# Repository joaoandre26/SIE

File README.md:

# SIE
Trabalho desenvolvido no âmbito da UC de Sistemas de Instrumentação em Eletrónica, 4º ano MIEET, ano lectivo 2018/19
Para esclarecer alguma dúvida relativamente ao trabalho desenvolvido na UC poderá contactar um dos membros do grupo por e-mail.

/*Examples*/
Na pasta MicrocontrollerExemple-master encontra-se codigo para o qual me baseei para escrever as funções do LCD. Muito Obrigado ao desenvolvedor, foi uma grande ajuda.
Link: https://github.com/andrade824/Microcontroller-Example-Code

/*Info/Reports*/
Na pasta reports encontra-se os relatorios de todas as fases deste projecto, bem como o manual de utilizador. Deverá encontrar no manual do utilizador todas as intruções para colocar o nosso projecto em total funcionamento.

/*Elevator_PCB*/
Na pasta elevatorpcb encontra-se os gerber files para imprimir o nosso pcb, e os esquemas de montagem por nós utilizados.

/*Code*/
Na pasta Elevator_Code encontra o codigo referente ao projecto 0, assim como a versão final funcional de codigo para colocar no elevador. Existem alguns erros no codigo que poderão virificar em detalhe no report da fase 3.

Notas:
O trabalho desenvolvido que se encontra neste repositório está completamente funcional, não contemplando todas as especificações exigidas inicialmente, é o suficiente para colocar o elevador a subir e descer para qualquer um dos andares.

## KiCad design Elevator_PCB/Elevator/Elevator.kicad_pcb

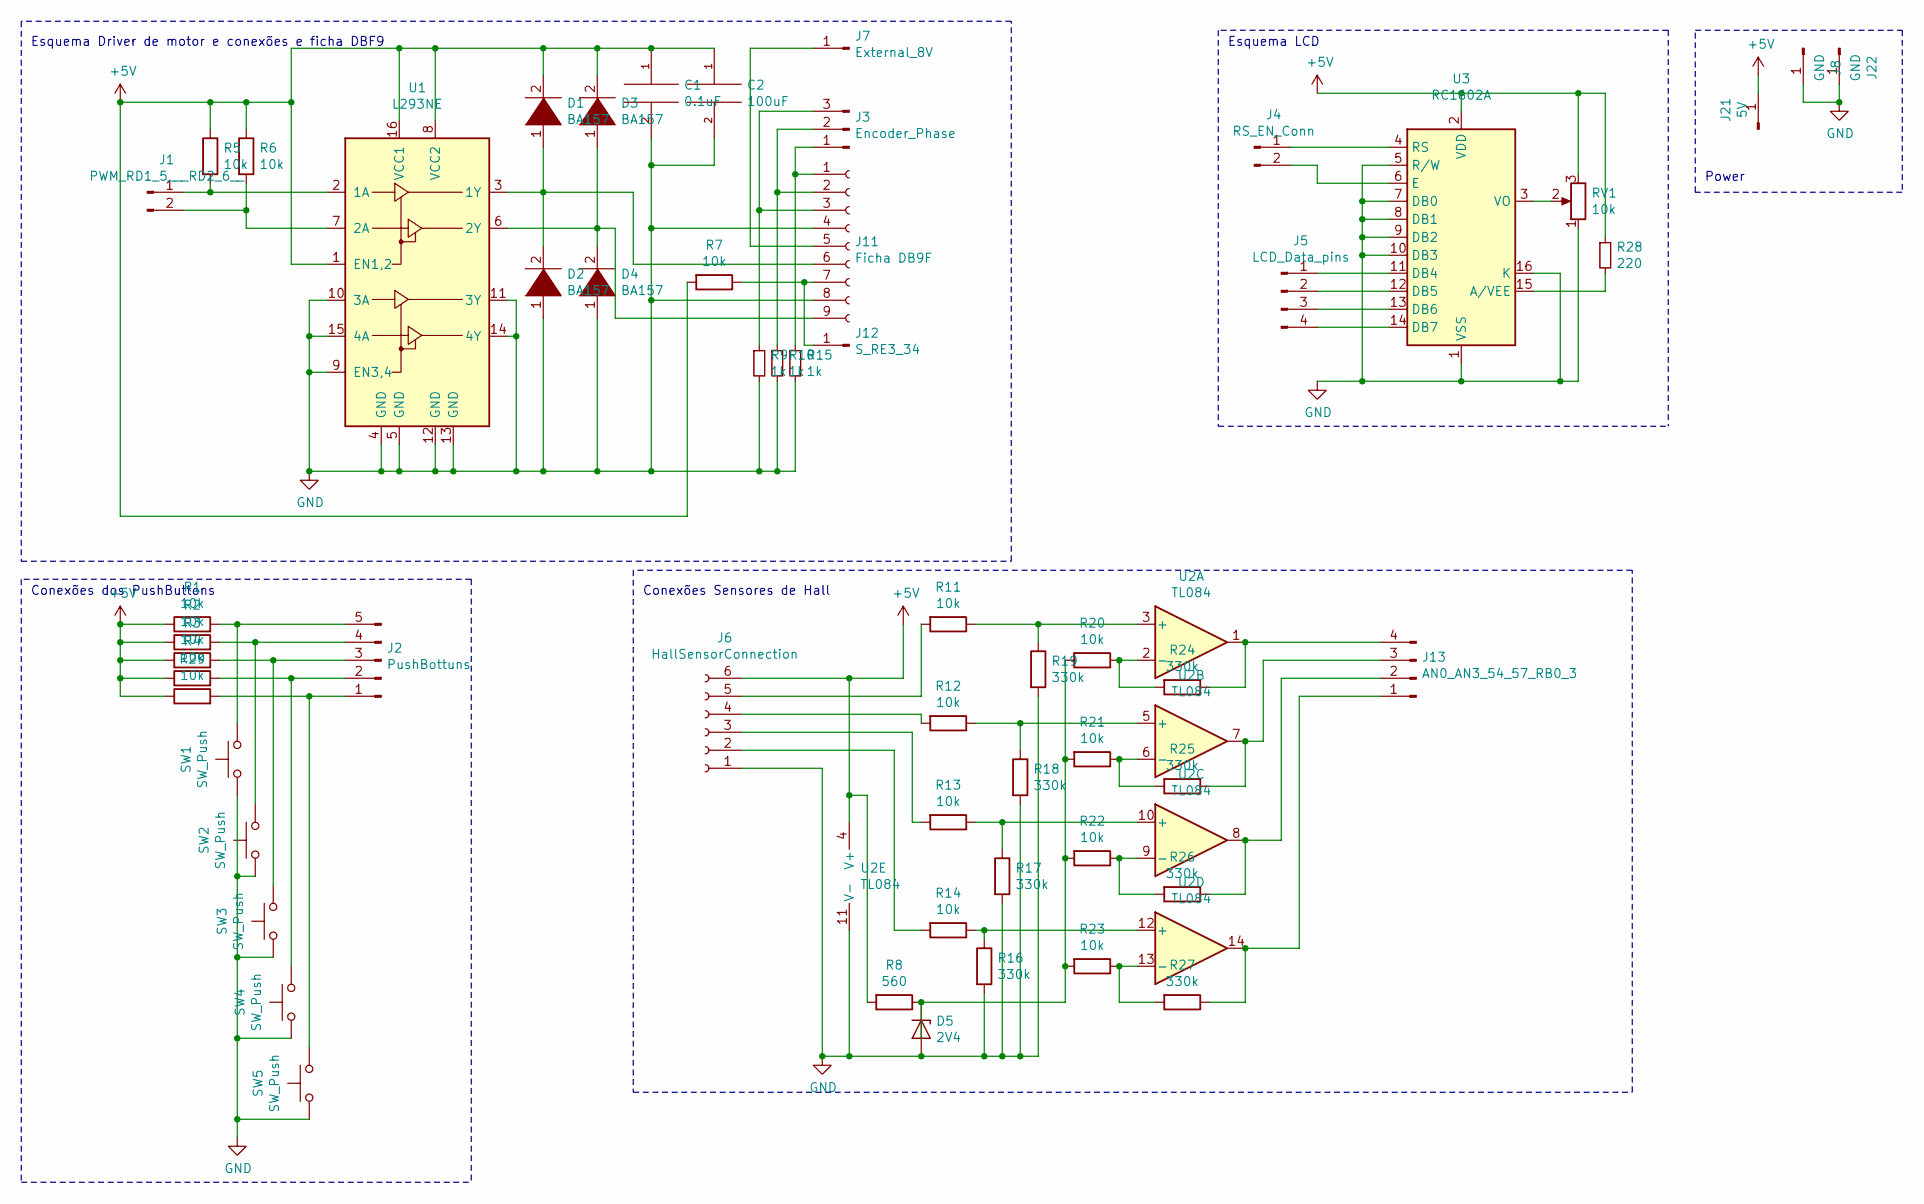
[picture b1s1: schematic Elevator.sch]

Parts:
C1: 0.1uF; CP_Axial_L11.0mm_D6.0mm_P18.00mm_Horizontal
C2: 100uF; CP_Axial_L11.0mm_D6.0mm_P18.00mm_Horizontal
D1, D2, D3, D4: BA157; D_DO-41_SOD81_P7.62mm_Horizontal
D5: 2V4; D_DO-35_SOD27_P7.62mm_Horizontal
J1: PWM_RD1_5___RD2_6__; PinHeader_1x02_P2.54mm_Vertical
J2: PushBottuns; PinHeader_1x05_P2.54mm_Vertical
J3: Encoder_Phase; PinHeader_1x03_P2.54mm_Vertical
J4: RS_EN_Conn; PinHeader_1x02_P2.54mm_Vertical
J5: LCD_Data_pins; PinHeader_1x04_P2.54mm_Vertical
J6: HallSensorConnection; PinHeader_1x06_P2.54mm_Vertical
J7: External_8V; PinHeader_1x01_P2.54mm_Vertical
J8, J22: GND; PinHeader_1x01_P2.54mm_Vertical
J11: Ficha DB9F; PinSocket_1x09_P2.54mm_Vertical
J12: S_RE3_34; PinHeader_1x01_P2.54mm_Vertical
J13: AN0_AN3_54_57_RB0_3; PinHeader_1x04_P2.54mm_Vertical
J21: 5V; PinHeader_1x01_P2.54mm_Vertical
R1, R2, R3, R4, R5, R6, R7, R11, R12, R13, R14, R20, R21, R22, R23, R29: 10k; R_Axial_DIN0207_L6.3mm_D2.5mm_P7.62mm_Horizontal
R8: 560; R_Axial_DIN0207_L6.3mm_D2.5mm_P7.62mm_Horizontal
R9, R10, R15: 1k; R_Axial_DIN0207_L6.3mm_D2.5mm_P7.62mm_Horizontal
R16, R17, R18, R19, R24, R25, R26, R27: 330k; R_Axial_DIN0207_L6.3mm_D2.5mm_P7.62mm_Horizontal
R28: 220; R_Axial_DIN0207_L6.3mm_D2.5mm_P7.62mm_Horizontal
RV1: 10k; Potentiometer_ACP_CA9-H5_Horizontal
SW1, SW2, SW3, SW4, SW5: SW_Push; SW_PUSH_6mm_H5mm
U1: L293NE; DIP-16_W7.62mm
U2: TL084; DIP-14_W7.62mm_Socket_LongPads
U3: RC1602A; PinSocket_1x17_P2.54mm_Vertical

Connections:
+5V: C1.1, C2.1, D1.2 (A), D3.2 (A), J6.6, J21.1, R1.1, R2.1, R3.1, R4.1, R5.1, R6.1, R7.2, R8.2, R28.1, R29.1, RV1.3, U1.1 (EN1,2), U1.8 (VCC2), U1.16 (VCC1), U2.4 (V+), U3.2 (VDD)
GND: C1.2, C2.2, D2.1 (K), D4.1 (K), D5.2 (A), J6.1, J8.1, J11.4, J11.8, J22.1, R9.2, R10.2, R15.2, R16.2, R17.2, R18.2, R19.2, RV1.1, SW1.1, SW2.1, SW3.1, SW4.1, SW5.1, U1.4 (GND), U1.5 (GND), U1.9 (EN3,4), U1.10 (3A), U1.11 (3Y), U1.12 (GND), U1.13 (GND), U1.14 (4Y), U1.15 (4A), U2.11 (V-), U3.1 (VSS), U3.5 (R/W), U3.7 (DB0), U3.8 (DB1), U3.9 (DB2), U3.10 (DB3), U3.16 (K)
unnamed: D1.1 (K), D2.2 (A), J11.6, U1.3 (1Y)
unnamed: D3.1 (K), D4.2 (A), J11.9, U1.6 (2Y)
unnamed: D5.1 (K), R8.1, R20.2, R21.2, R22.2, R23.2
unnamed: J1.1, R5.2, U1.2 (1A)
unnamed: J1.2, R6.2, U1.7 (2A)
unnamed: J2.1, R29.2, SW5.2
unnamed: J2.2, R4.2, SW4.2
unnamed: J2.3, R3.2, SW3.2
unnamed: J2.4, R2.2, SW2.2
unnamed: J2.5, R1.2, SW1.2
unnamed: J4.1, U3.4 (RS)
unnamed: J4.2, U3.6 (E)
unnamed: J5.1, U3.11 (DB4)
unnamed: J5.2, U3.12 (DB5)
unnamed: J5.3, U3.13 (DB6)
unnamed: J5.4, U3.14 (DB7)
unnamed: J6.2, R14.2
unnamed: J6.3, R13.2
unnamed: J6.4, R12.2
unnamed: J6.5, R11.2
unnamed: J3.1, J11.1, R15.1
unnamed: J3.2, J11.2, R10.1
unnamed: J3.3, J11.3, R9.1
unnamed: J7.1, J11.5
unnamed: J11.7, J12.1, R7.1
unnamed: J13.1, R27.1, U2.14
unnamed: J13.2, R26.1, U2.8
unnamed: J13.3, R25.1, U2.7
unnamed: J13.4, R24.1, U2.1
unnamed: R11.1, R19.1, U2.3 (+)
unnamed: R12.1, R18.1, U2.5 (+)
unnamed: R13.1, R17.1, U2.10 (+)
unnamed: R14.1, R16.1, U2.12 (+)
unnamed: R20.1, R24.2, U2.2 (-)
unnamed: R21.1, R25.2, U2.6 (-)
unnamed: R22.1, R26.2, U2.9 (-)
unnamed: R23.1, R27.2, U2.13 (-)
unnamed: R28.2, U3.15 (A/VEE)
unnamed: RV1.2, U3.3 (VO)

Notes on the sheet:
Esquema Driver de motor e conexões e ficha DBF9
Conexões dos PushButtons
Esquema LCD
Conexões Sensores de Hall
Power

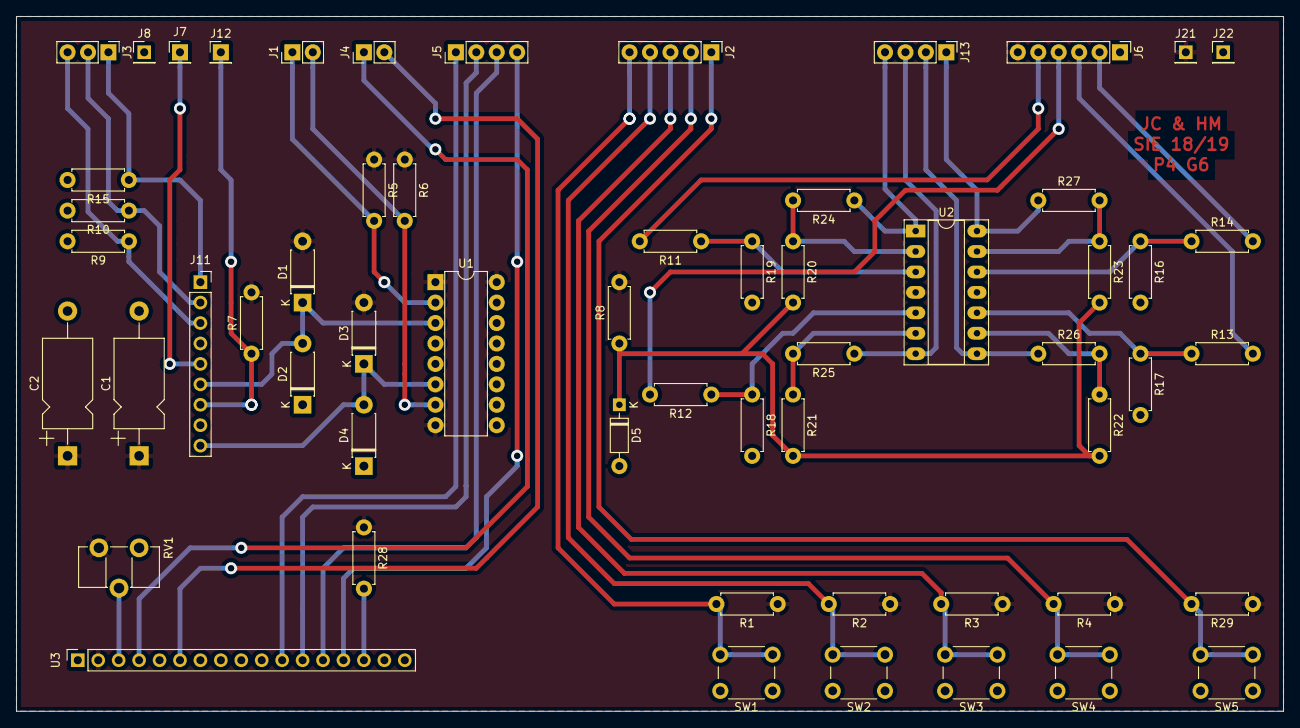
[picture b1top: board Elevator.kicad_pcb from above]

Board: 2 copper layers, 157.5 x 86.4 mm, 58 parts (0 on the bottom side), 41 nets.

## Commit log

2019-09-18 README update
2019-09-18 PCB stuff
2019-09-18 Reports update
2019-09-18 Exemple code used to write code for the LCD
2019-09-18 Project 0 and final version of the code
2019-09-18 update final README
